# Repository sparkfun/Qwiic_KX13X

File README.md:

SparkFun Triple-Axis Accelerometer Breakout - KX13x (Qwiic)
========================================

<table class="table table-hover table-striped table-bordered">
    <tr align="center">
      <td></td>
      <td></td>
    </tr>
    <tr align="center">
      <td><a href="https://www.sparkfun.com/products/17871">SparkFun Triple-Axis Accelerometer Breakout - KX132 (Qwiic)</a></td>
      <td><a href="https://www.sparkfun.com/products/17589">SparkFun Triple-Axis Accelerometer Breakout - KX134 (Qwiic)</a></td>
    </tr>
</table>

The Triple-Axis Accelerometer Breakout - KX132 & KX134 (Qwiic) are simple Qwiic breakouts for a pair of high-speed digital accelerometers from Kionix. Both accelerometers have four user-selectable ranges (KX132: &plusmn;2/4/8/16g & KX134: &plusmn;8/16/32/64g) with sensitivity as high as 17367 counts/g @&plusmn;2g (highest KX134 setting is 4424 counts/g @&plusmn;8g) and Output Data Rate up to 25600Hz. The KX134 and KX132 also feature a host of accelerometer features including Freefall detection, Directional Tap<sup>&trade;</sup> and Double-Tap<sup>&trade;</sup> detection, tilt orientation detection and more.

Repository Contents
-------------------

* **/Documentation** - Data sheets, additional product information
* **/Hardware** - Eagle design files (.brd, .sch)
* **/Production** - Production panel files (.brd)

Documentation
--------------
* **[SparkFun Qwiic KX13x Library](https://github.com/sparkfun/SparkFun_KX13X_Arduino_Library)** - Arduino library for the Triple-Axis Accelerometer Breakout - KX13x (Qwiic).
* **[SparkFun Qwiic KX13x_Py](https://github.com/sparkfun/Qwiic_KX13X_Py)** - Python module for the Triple-Axis Accelerometer Breakout - KX13x (Qwiic).
* **[Hookup Guide](https://learn.sparkfun.com/tutorials/triple-axis-accelerometer-breakout---kx13x-qwiic-hookup-guide-)** - Basic hookup guide for the Triple-Axis Accelerometer Breakout - KX13x (Qwiic).

Product Versions
----------------
* [SEN-17871](https://www.sparkfun.com/products/17871) - KX132 Version initial release (v10).
* [SEN-17589](https://www.sparkfun.com/products/17589) - KX134 Version initial release (v10).

License Information
-------------------

This product is _**open source**_! 

Please review the LICENSE.md file for license information. 

If you have any questions or concerns on licensing, please contact technical support on our [SparkFun forums](https://forum.sparkfun.com/viewforum.php?f=152).

Distributed as-is; no warranty is given.

- Your friends at SparkFun.

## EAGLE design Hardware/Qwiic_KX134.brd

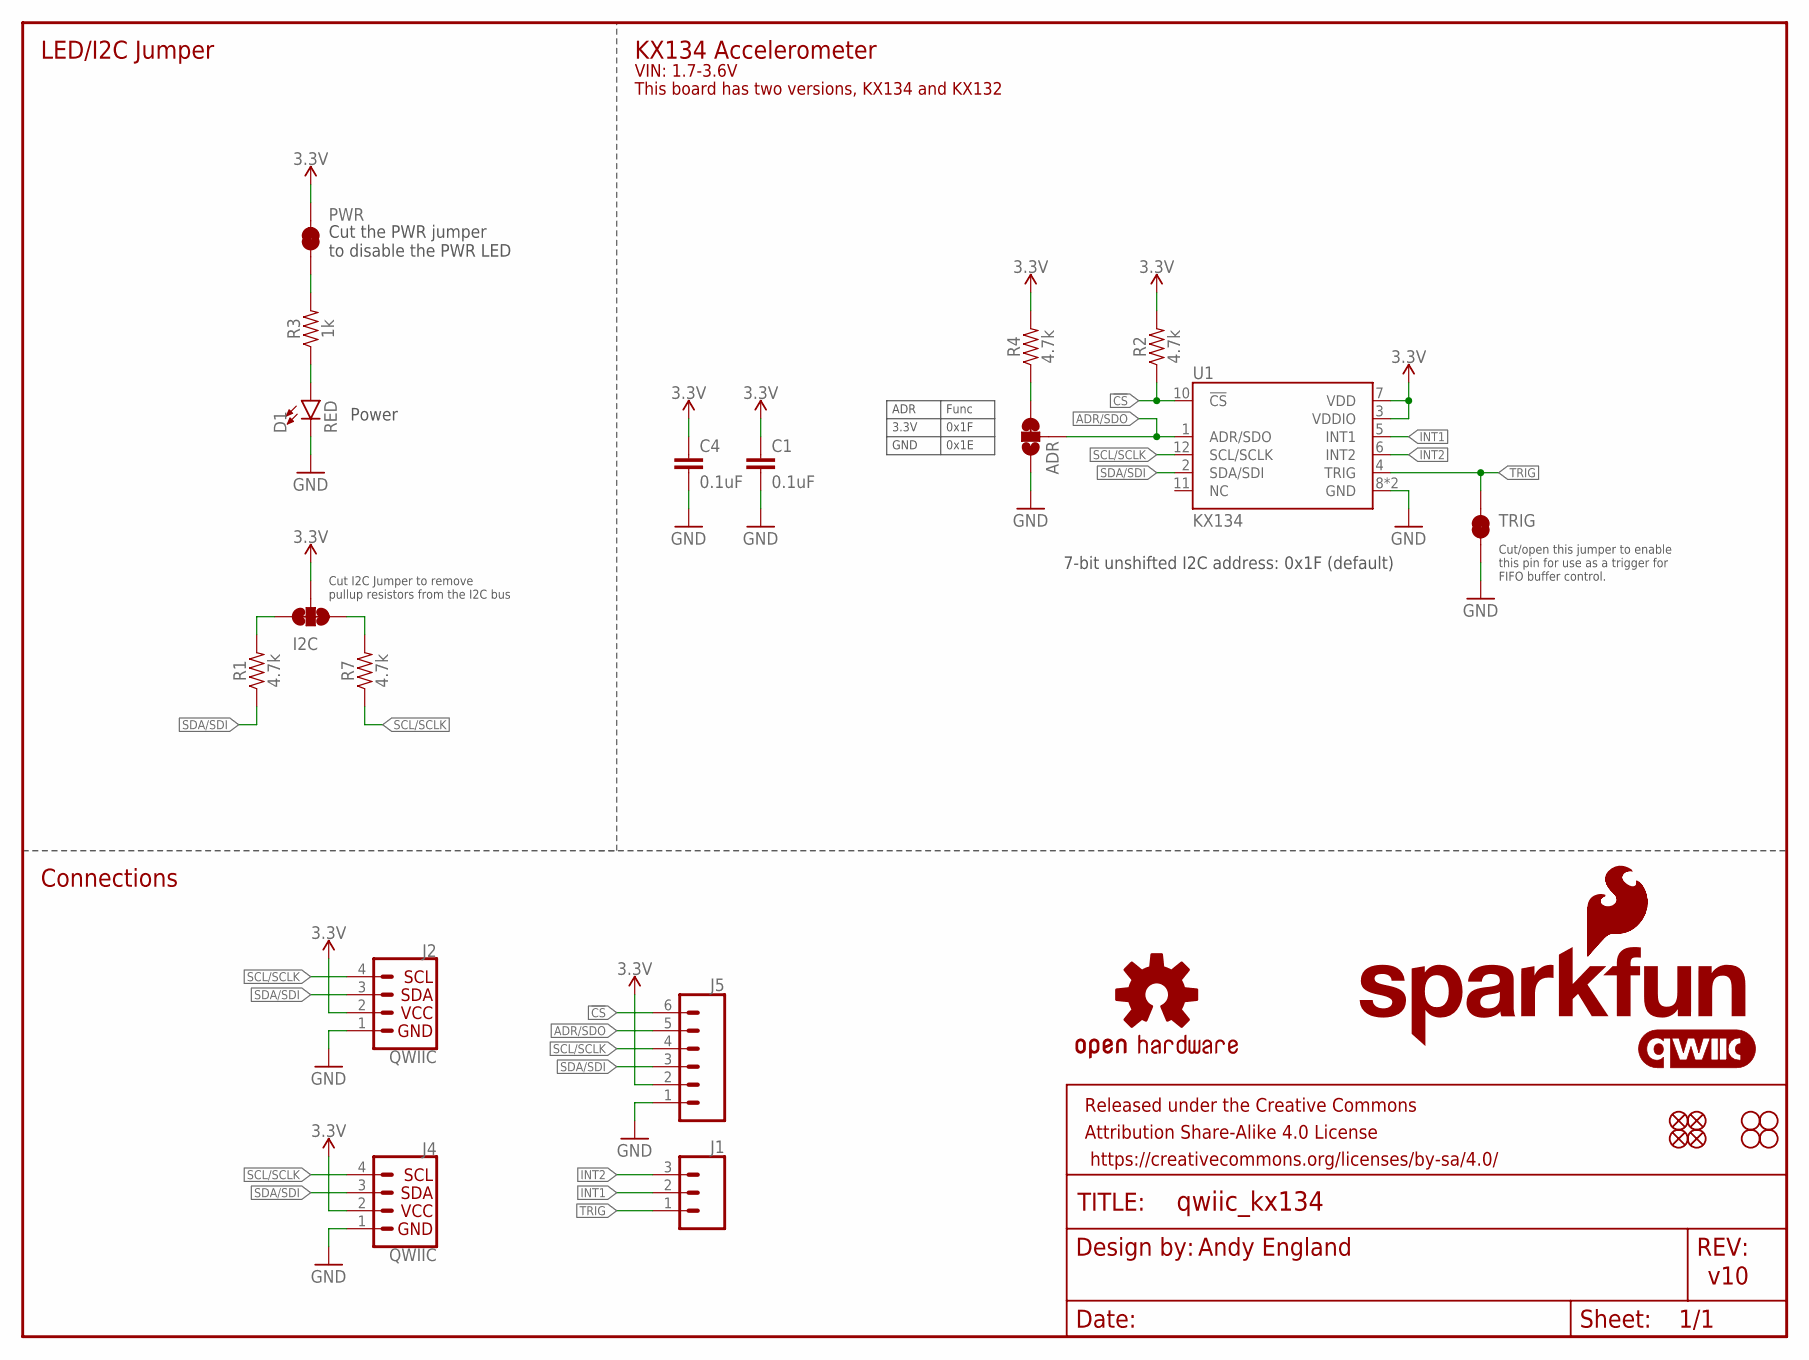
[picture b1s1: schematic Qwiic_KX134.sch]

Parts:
ADR: JUMPER-SMT_3_1-NC_TRACE_SILK; SMT-JUMPER_3_1-NC_TRACE_SILK
C1, C4: 0.1uF; 0603
D1: RED; LED-0603
FRAME1: FRAME-LETTER; CREATIVE_COMMONS
I2C: JUMPER-SMT_3_2-NC_TRACE_SILK; SMT-JUMPER_3_2-NC_TRACE_SILK
J1: CONN_031X03_NO_SILK; 1X03_NO_SILK
J2, J4: QWIIC; JST04_1MM_RA
J5: CONN_06NO_SILK_NO_POP; 1X06_NO_SILK
JP1, JP2, JP5, JP6: FIDUCIALUFIDUCIAL; MICRO-FIDUCIAL
JP3, JP4, JP7, JP8: STAND-OFF
LOGO1, LOGO2: SFE_LOGO_FLAME.1_INCH; SFE_LOGO_FLAME_.1
LOGO3: QWIIC_LOGO_4MM; QWIIC_4MM
LOGO4: SFE_LOGO_NAME_FLAME.1_INCH; SFE_LOGO_NAME_FLAME_.1
LOGO5: OSHW-LOGOS; OSHW-LOGO-S
PWR: JUMPER-SMT_2_NC_TRACE_SILK; SMT-JUMPER_2_NC_TRACE_SILK
R1, R2, R4, R7: 4.7k; 0603
R3: 1k; 0603
TRIG: JUMPER-SMT_2_NC_TRACE_SILK; SMT-JUMPER_2_NC_TRACE_SILK
U1: KX134; KX13X

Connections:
3.3V: C1.1, C4.1, I2C.2, J2.2, J4.2, J5.2, PWR.2, R2.2, R4.2, U1.3 (VDDIO), U1.7 (VDD)
!CS: J5.6, R2.1, U1.10 (!CS)
ADR/SDO: ADR.2, J5.5, U1.1 (ADR/SDO)
GND: ADR.1, C1.2, C4.2, D1.C, J2.1, J4.1, J5.1, TRIG.2, U1.8 (GND), U1.9 (GND)
INT1: J1.2, U1.5 (INT1)
INT2: J1.3, U1.6 (INT2)
unnamed: PWR.1, R3.2
unnamed: I2C.3, R1.2
unnamed: D1.A, R3.1
unnamed: I2C.1, R7.2
unnamed: ADR.3, R4.1
SCL/SCLK: J2.4, J4.4, J5.4, R7.1, U1.12 (SCL/SCLK)
SDA/SDI: J2.3, J4.3, J5.3, R1.1, U1.2 (SDA/SDI)
TRIG: J1.1, TRIG.1, U1.4 (TRIG)

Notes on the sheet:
v10
7-bit unshifted I2C address: 0x1F (default)
Power
Cut the PWR jumper to disable the PWR LED
Andy England
Cut I2C Jumper to remove pullup resistors from the I2C bus
Cut/open this jumper to enable this pin for use as a trigger for FIFO buffer control.
ADR
Func
3.3V
0x1F
0x1E
GND
KX134 Accelerometer
VIN: 1.7-3.6V
LED/I2C Jumper
Connections
This board has two versions, KX134 and KX132

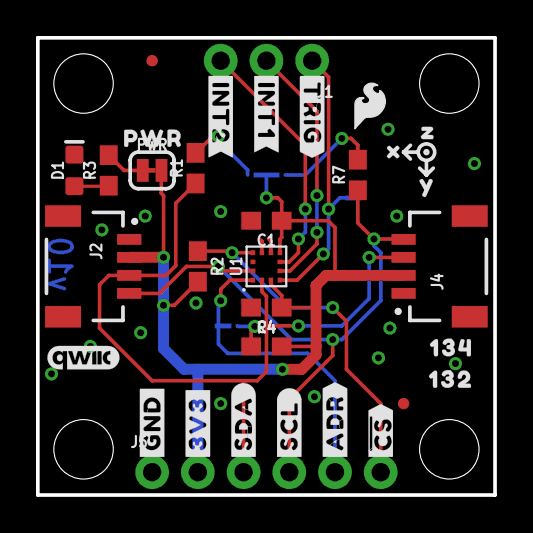
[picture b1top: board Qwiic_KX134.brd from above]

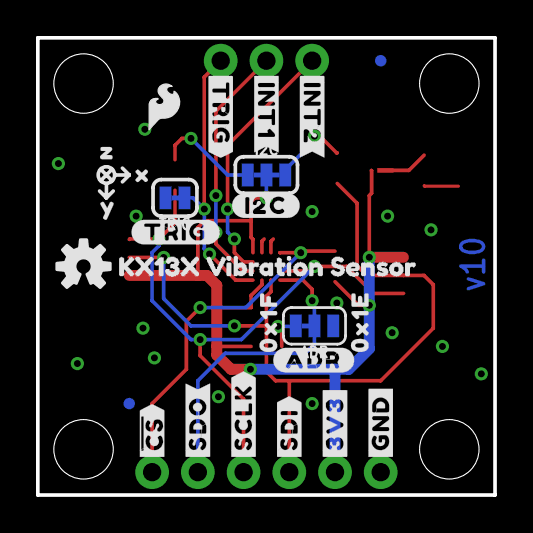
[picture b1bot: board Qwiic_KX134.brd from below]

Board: 2 copper layers, 25.4 x 25.4 mm, 64 parts (25 on the bottom side), 14 nets.

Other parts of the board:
U$1, U$28: X0
U$2: #SCL#0
U$3: #SDA#0
U$4, U$5: #3V3#0
U$6, U$7: #GND#0
U$8, U$9: ##CS##0
U$10: #ADR#0
U$11, U$15: #TRIG#0
U$12, U$13: #INT1#0
U$14: 0X1E0
U$16: KX13X_VIBRATION_SENSOR0
U$17: #TRIG#2
U$18, U$19: #INT2#0
U$20: #ADR#3
U$21, U$29: Y0
U$22: #I2C#0
U$23: 0X1F0
U$24: #SDI#0
U$25: #SCLK#0
U$26: #SDO#0
U$30, U$32: Z0
U$31: PWR0
U$33: 1320
U$34: 1340

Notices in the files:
parts and their libraries:
SparkFun-Resistors: Licensing: Creative Commons ShareAlike 4.0 International - https://creativecommons.org/licenses/by-sa/4.0
SparkFun-Aesthetics: Released under the Creative Commons Attribution Share-Alike 4.0 License
SparkFun-Aesthetics: https://creativecommons.org/licenses/by-sa/4.0
